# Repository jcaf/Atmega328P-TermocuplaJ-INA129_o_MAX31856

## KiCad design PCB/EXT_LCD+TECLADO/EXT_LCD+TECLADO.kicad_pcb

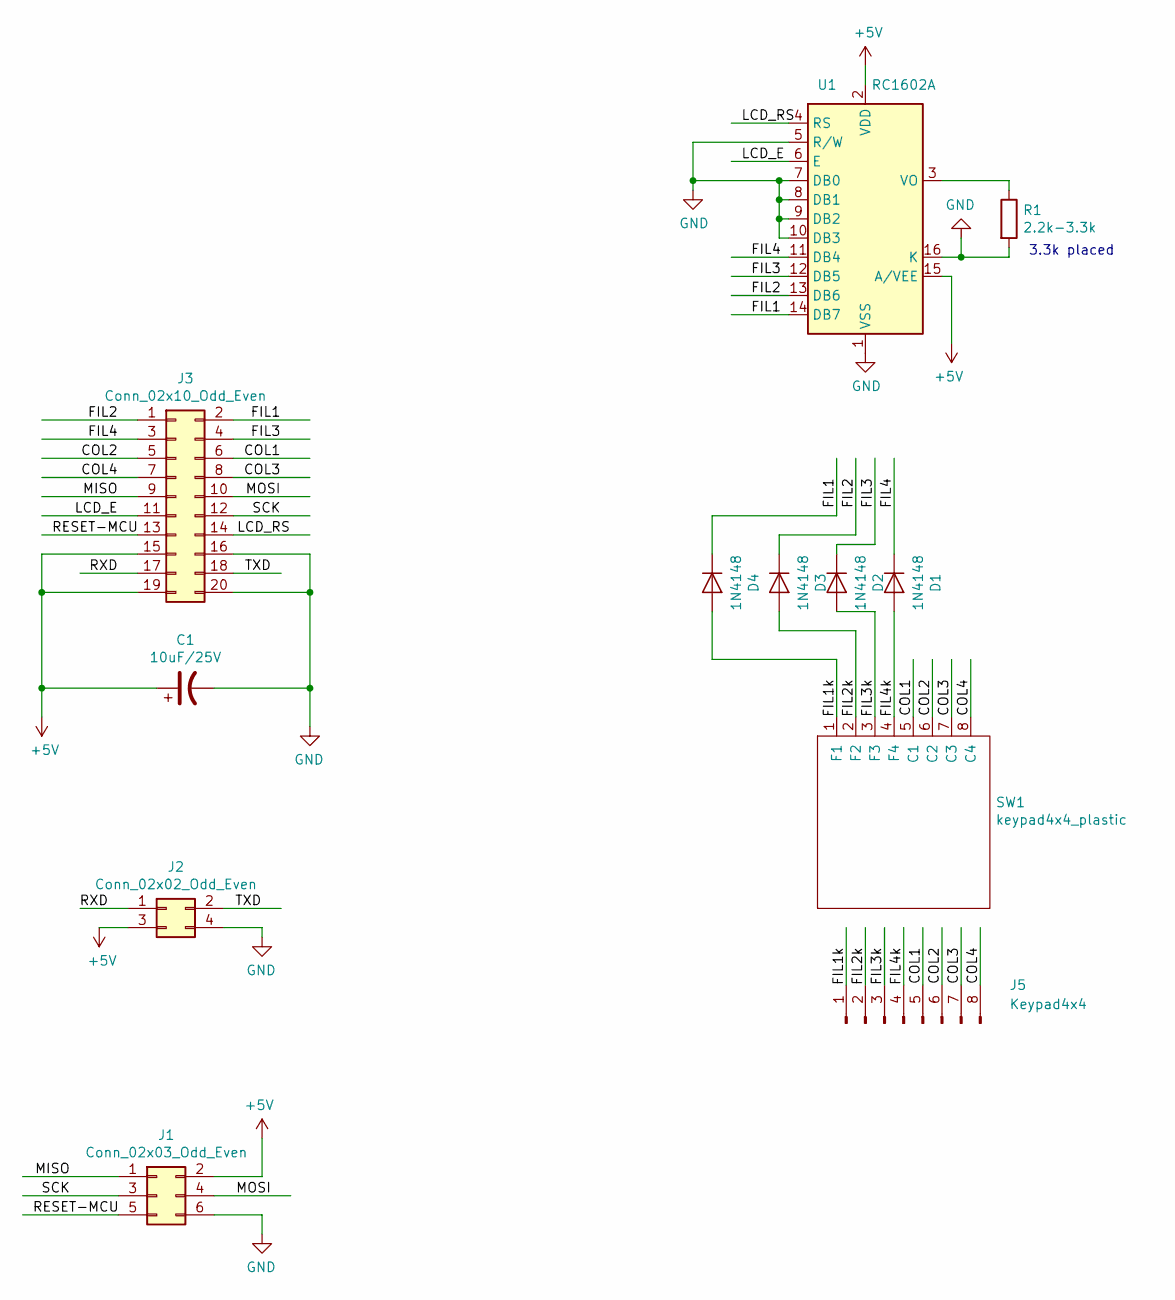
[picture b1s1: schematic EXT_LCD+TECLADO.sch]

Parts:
C1: 10uF/25V; CP_Radial_D5.0mm_P2.50mm
D1, D2, D3, D4: 1N4148; D_DO-35_SOD27_P7.62mm_Horizontal
J1: Conn_02x03_Odd_Even; IDC-Header_2x03_P2.54mm_Vertical
J2: Conn_02x02_Odd_Even; PinHeader_2x02_P2.54mm_Vertical
J3: Conn_02x10_Odd_Even; IDC-Header_2x10_P2.54mm_Vertical_Lock
J5: Keypad4x4; PinHeader_1x08_P2.54mm_Vertical
R1: 2.2k-3.3k; R_Axial_DIN0207_L6.3mm_D2.5mm_P10.16mm_Horizontal
SW1: keypad4x4_plastic
U1: RC1602A; WC1602A

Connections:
+5V: C1.1, J1.2, J2.3, J3.15, J3.19, U1.2 (VDD), U1.15 (A/VEE)
/COL1: J3.6, J5.5, SW1.5 (C1)
/COL2: J3.5, J5.6, SW1.6 (C2)
/COL3: J3.8, J5.7, SW1.7 (C3)
/COL4: J3.7, J5.8, SW1.8 (C4)
/FIL1: D4.1 (K), J3.2, U1.14 (DB7)
/FIL1k: D4.2 (A), J5.1, SW1.1 (F1)
/FIL2: D3.1 (K), J3.1, U1.13 (DB6)
/FIL2k: D3.2 (A), J5.2, SW1.2 (F2)
/FIL3: D2.1 (K), J3.4, U1.12 (DB5)
/FIL3k: D2.2 (A), J5.3, SW1.3 (F3)
/FIL4: D1.1 (K), J3.3, U1.11 (DB4)
/FIL4k: D1.2 (A), J5.4, SW1.4 (F4)
/LCD_E: J3.11, U1.6 (E)
/LCD_RS: J3.14, U1.4 (RS)
/MISO: J1.1, J3.9
/MOSI: J1.4, J3.10
/RESET-MCU: J1.5, J3.13
/RXD: J2.1, J3.17
/SCK: J1.3, J3.12
/TXD: J2.2, J3.18
GND: C1.2, J1.6, J2.4, J3.16, J3.20, R1.2, U1.1 (VSS), U1.5 (R/W), U1.7 (DB0), U1.8 (DB1), U1.9 (DB2), U1.10 (DB3), U1.16 (K)
unnamed: R1.1, U1.3 (VO)

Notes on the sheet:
3.3k placed

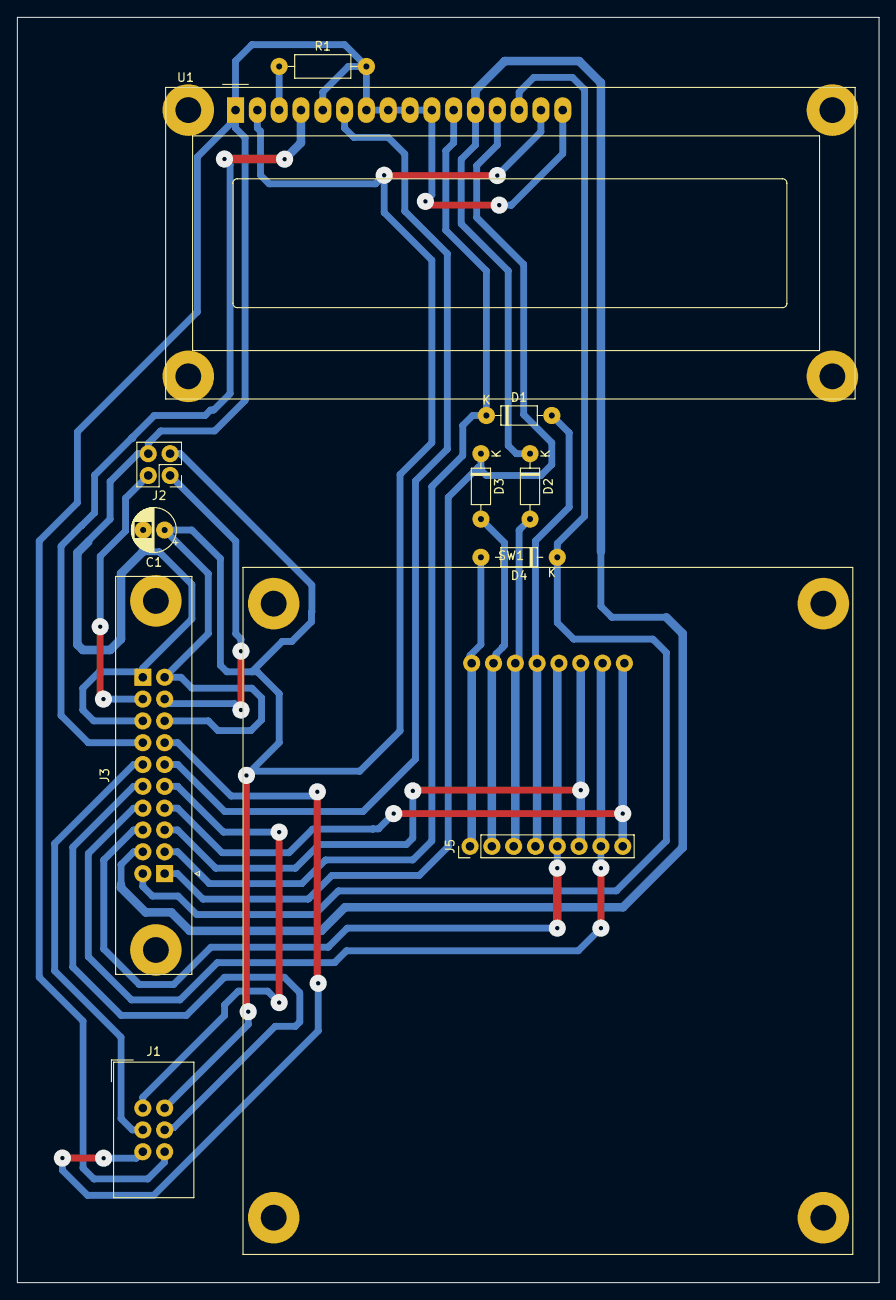
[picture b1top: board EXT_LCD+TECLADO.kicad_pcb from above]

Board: 2 copper layers, 100.3 x 147.3 mm, 12 parts (0 on the bottom side), 23 nets.

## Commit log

2019-04-30 Antes de intercambiar Relay1 y Relay2. Para minimizar los arcos producidos por los relays Todo lo demas ok.
2019-04-30 INtercambiando relay1 y relay2...
2019-04-30 Corregido el bug de salir del menu y reseteaba el contador de minutos. Este hex es el que ha sido grabado a los 3 cktos con sus respectivo MAX31856
2019-05-01 nueva calibracion de ktes PID OK probado con el INA129
2019-05-01 FINAL ENTREGADO
2019-05-01 11-PINS SOCKET PINOUT
